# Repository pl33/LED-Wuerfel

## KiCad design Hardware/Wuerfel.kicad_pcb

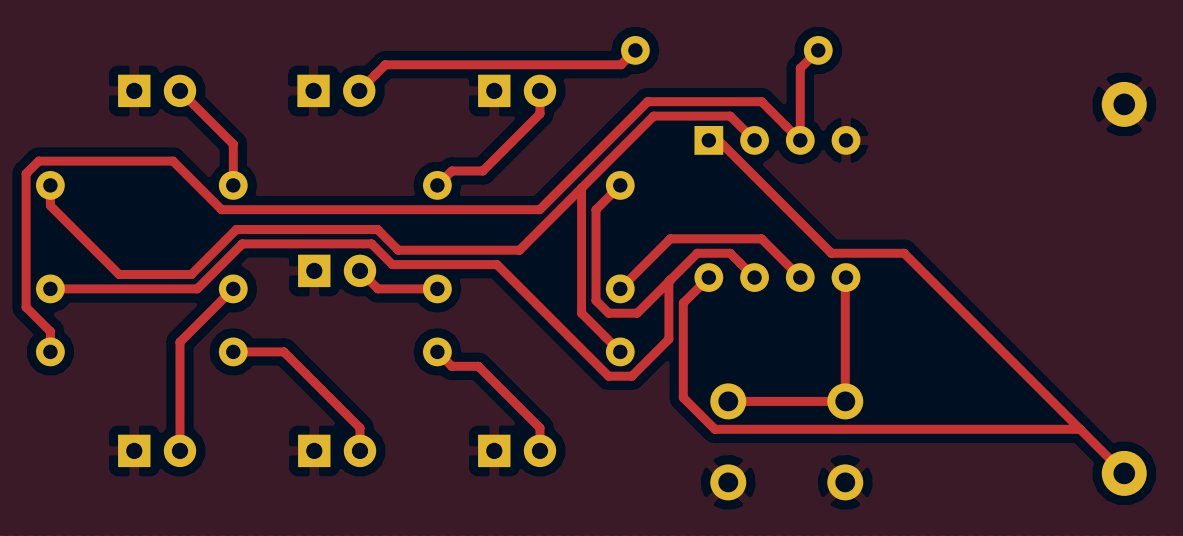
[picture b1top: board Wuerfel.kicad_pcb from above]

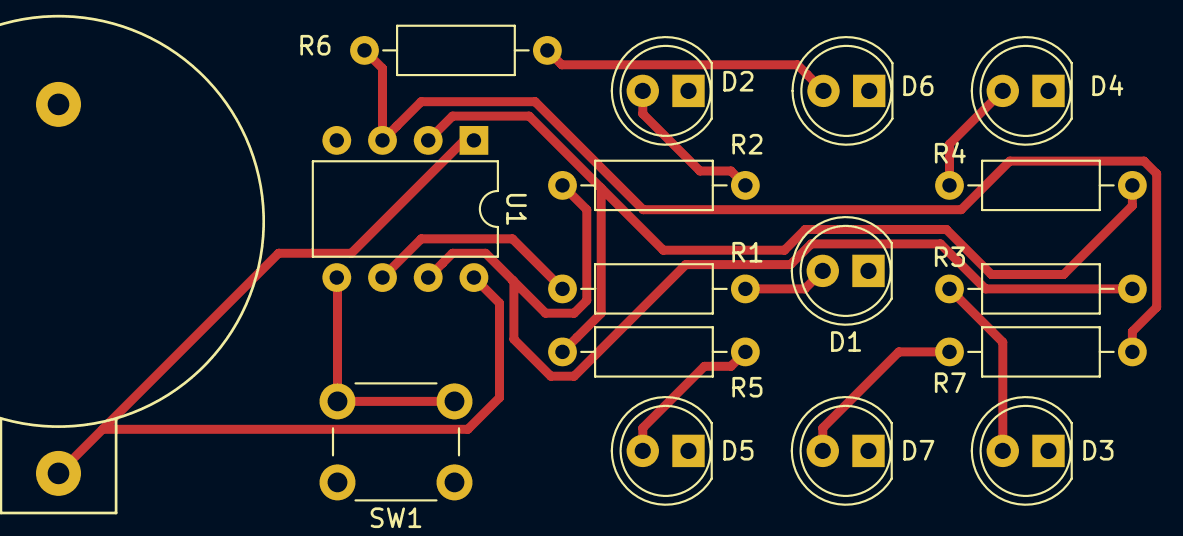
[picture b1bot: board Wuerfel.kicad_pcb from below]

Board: 2 copper layers, 17 parts (17 on the bottom side), 14 nets.

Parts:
BT1: 3V Li-Cell; KZH20-1
D1, D2, D3, D4, D5, D6, D7: LED; LED_D5.0mm
R1, R2, R3, R4, R5, R6, R7: 100R; R_Axial_DIN0207_L6.3mm_D2.5mm_P10.16mm_Horizontal
SW1: SW_Push; SW_PUSH_6mm_H7.3mm
U1: ATTINY13A-PU; DIP-8_W7.62mm

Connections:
/+3V: BT1.1, U1.1, U1.8
GND: BT1.2, D1.1, D2.1, D3.1, D4.1, D5.1, D6.1, D7.1, SW1.1, U1.4
unnamed: D1.2, R1.2
unnamed: D2.2, R2.2
unnamed: D3.2, R3.2
unnamed: D4.2, R4.2
unnamed: D5.2, R5.2
unnamed: D6.2, R6.2
unnamed: D7.2, R7.2
unnamed: R1.1, U1.6
unnamed: R2.1, R3.1, U1.7
unnamed: R4.1, R5.1, U1.2
unnamed: R6.1, R7.1, U1.3
unnamed: SW1.2, U1.5

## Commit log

2018-03-17 Changed footprint of resistors; re-routing
2018-03-29 Release-candidate
2018-03-29 Added license
2018-08-27 Enlarged drill diameter of KZH20-1
2018-08-27 Migrated to KiCAD 5.0; Changed drill diameter of KZH20-1
